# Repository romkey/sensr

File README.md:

# Sensr

Sensr is a group of hardware projects intended for environmental
sensing.

It currently consists of:
- base board - ESP32-S3 with accelerometer, I2S microphone header, display header, 2 Qwiic ports, particle counter connector
- air - SCD40 CO2 + BME680 temperature/humidity/pressure sensor
- air-stcc4 - new STCC4 CO2 sensor + SHT40 temperature/humidity sensor
- light - TSL25911 light
- light-ltr390uv - LTR390 UV sensor + TSL25911 light sensor

Sensr is an ESP32 S3-based microcontroller intended for environmental sensing, as well as separate sensor boards.

## I2C Addresses

0x29 TSL25911
0x74 AS7331
0x49 AS7341
0x53 LT-390 

0x76 BME680
0x62 SCD40
0x59 SGP40
0x5D SFA30
0x44 SHT3X-D

0x6A LSM6DS3TR-C 

Gas:
0x64
0x65
0x66
0x67
0x68
0x69
0x6B

# bodged I2S
SCK - CS - 10
SD - RESET - 9
WS - DC - 46
L/R - SDI (MOSI) - 16

## License

Hardware is shared under the [CERN-OHL-S-2.0](CERN_OHL_S_v2.txt) license.

Software is shared under the [MIT license](MIT-LICENSE.txt).

Documentation is shared under the [CC-BY-SA-4.0](CC-BY-SA-4.0.txt) - Attribution-ShareAlike license.

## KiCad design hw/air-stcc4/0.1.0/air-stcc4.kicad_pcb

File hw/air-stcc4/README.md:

# Sensr Air STCC4

This breakout board has Sensirion's new CO2 sensor, the STCC4, as well as an SHT40 temperature/humidity sensor. The board also has two STEMMAQT/Qwiic connectors and a five pin header with power, I2C and the STCC4's address select pin.

This is a 3.3V board and has no voltage regulator, so don't use it with 5V circuits!

It also has a power LED.

The STCC4 has a selectable I2C address depending on the state of the ADDR line.  The ADDR line has a weak pulldown resistor so that the STCC4's default I2C address is 0x64. If ADDR is high, the address will be 0x65.

The SHT40 is not directly accessible from the I2C bus. Instead it connects to a private second I2C bus with the STCC4. Its values may be read through the STCC4.

## 0.1.0 Hardware

## Firmware

Example program in CircuitPython:

```
import time
import board
import busio
from adafruit_stcc4 import STCC4

# Initialize I2C bus
i2c = busio.I2C(board.SCL, board.SDA)

# Initialize STCC4 sensor
sensor = STCC4(i2c)

print("STCC4 CO2 Sensor Test")
print("=" * 50)

# Print sensor information
print(f"Serial Number: {sensor.serial_number}")
print(f"Firmware Version: {sensor.firmware_version[0]}.{sensor.firmware_version[1]}")
print(f"SHT40 Available: {sensor.sht40_available}")
print()

# Read CO2, temperature, and humidity measurements
print("Environmental Measurements:")
print("-" * 30)

while True:
    co2 = sensor.co2
    print(f"Reading {i+1:2d}: CO2: {co2:6.1f} ppm")
        
    if sensor.sht40_available:
       temperature, humidity = sensor.measure_temperature_humidity()
       print(f"           Temp: {temperature:5.1f}°C, Humidity: {humidity:5.1f}%")
    else:
       print("           SHT40 not available - no temp/humidity data")
        
    print()
        
    time.sleep(2)  # Wait 2 seconds between readings

print("Test complete!")
```

## License

Hardware is shared under the [CERN-OHL-S-2.0](CERN_OHL_S_v2.txt) license.

Software is shared under the [MIT license](MIT-LICENSE.txt).

Documentation is shared under the [CC-BY-SA-4.0](CC-BY-SA-4.0.txt) - Attribution-ShareAlike license.

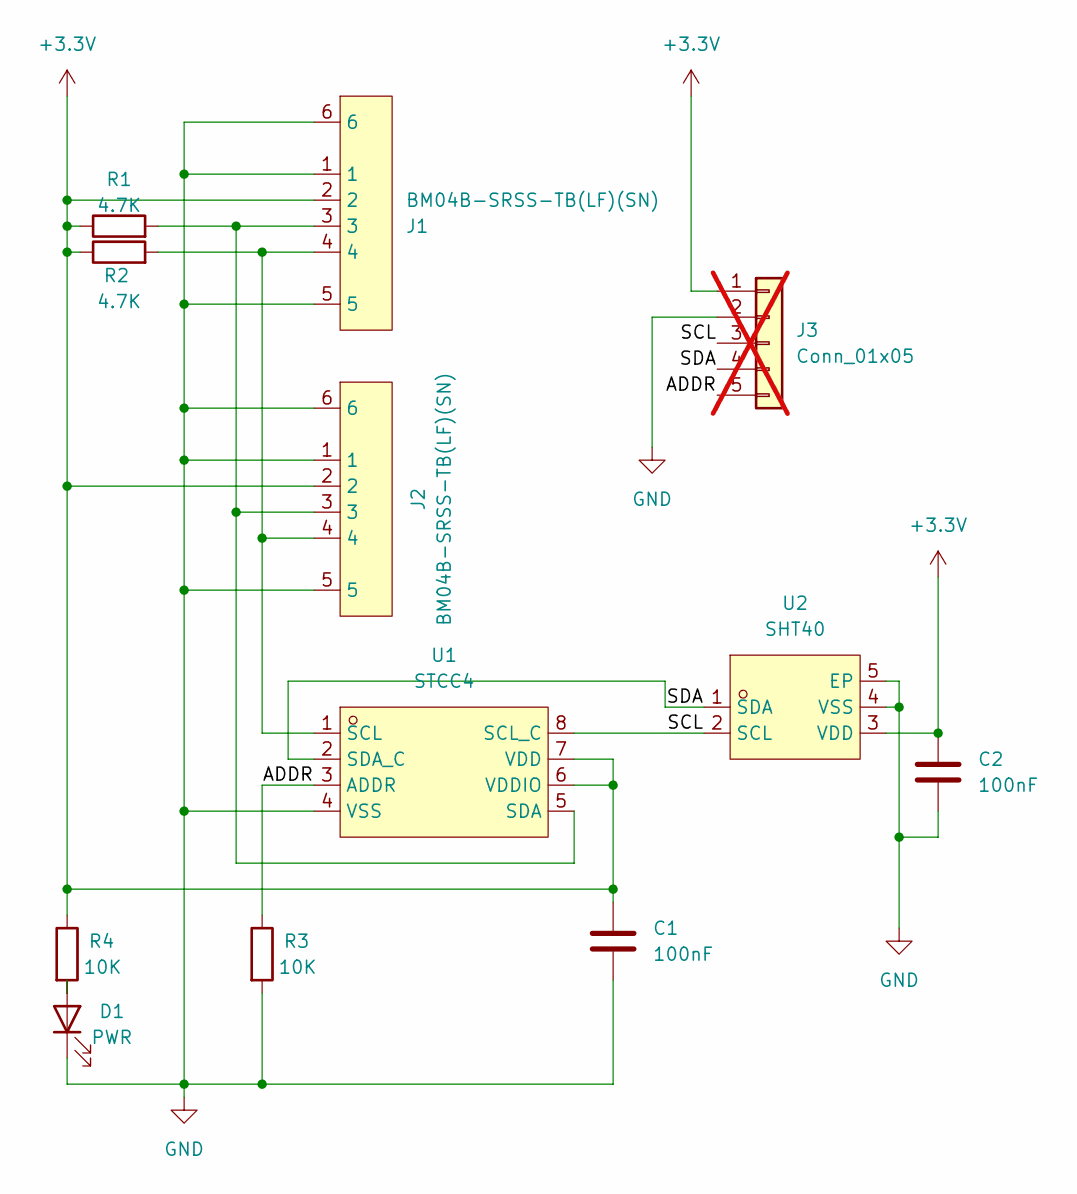
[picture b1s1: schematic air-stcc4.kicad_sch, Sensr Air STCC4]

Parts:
C1, C2: 100nF; C_0603_1608Metric_Pad1.08x0.95mm_HandSolder; MPN C14663
D1: PWR; LED_0201_0603Metric_Pad0.64x0.40mm_HandSolder; LCSC C2286
J1, J2: BM04B-SRSS-TB(LF)(SN); CONN-SMD_4P-P1.00_SM04B-SRSS-TB-LF-SN; LCSC Part C160404
J3: Conn_01x05; PinSocket_1x05_P2.54mm_Vertical; not fitted
R1, R2: 4.7K; R_0603_1608Metric_Pad0.98x0.95mm_HandSolder; MPN C23162
R3, R4: 10K; R_0603_1608Metric_Pad0.98x0.95mm_HandSolder; LCSC C25804
U1: STCC4; LAG-8_L4.0-W3.0-P1.15-TL; LCSC Part C49191471
U2: SHT40; DFN-4_L1.5-W1.5-P0.80-TL-EP; LCSC Part C7461861

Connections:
+3.3V: C1.1, C2.1, J1.2, J2.2, J3.1, R1.1, R2.1, R4.1, U1.6 (VDDIO), U1.7 (VDD), U2.3 (VDD)
/ADDR: J3.5, R3.1, U1.3 (ADDR)
/SCL: J3.3, U1.8 (SCL_C), U2.2 (SCL)
/SDA: J3.4, U1.2 (SDA_C), U2.1 (SDA)
GND: C1.2, C2.2, D1.1 (K), J1.1, J1.5, J1.6, J2.1, J2.5, J2.6, J3.2, R3.2, U1.4 (VSS), U2.4 (VSS), U2.5 (EP)
unnamed: D1.2 (A), R4.2
unnamed: J1.4, J2.4, R2.2, U1.1 (SCL)
unnamed: J1.3, J2.3, R1.2, U1.5 (SDA)

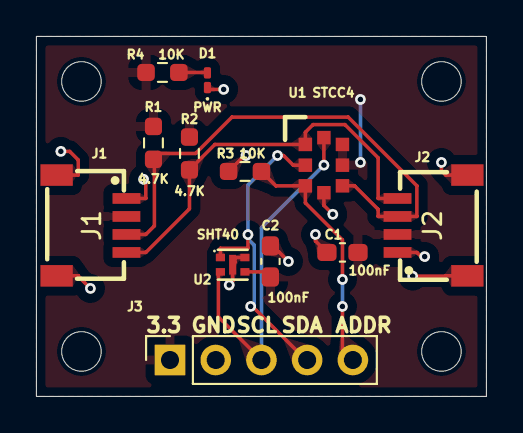
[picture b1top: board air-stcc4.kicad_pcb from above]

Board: 2 copper layers, 25.0 x 20.0 mm, 16 parts (0 on the bottom side), 8 nets.

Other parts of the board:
M1, M2, M3, M4: MountingHole_2.2mm_M2

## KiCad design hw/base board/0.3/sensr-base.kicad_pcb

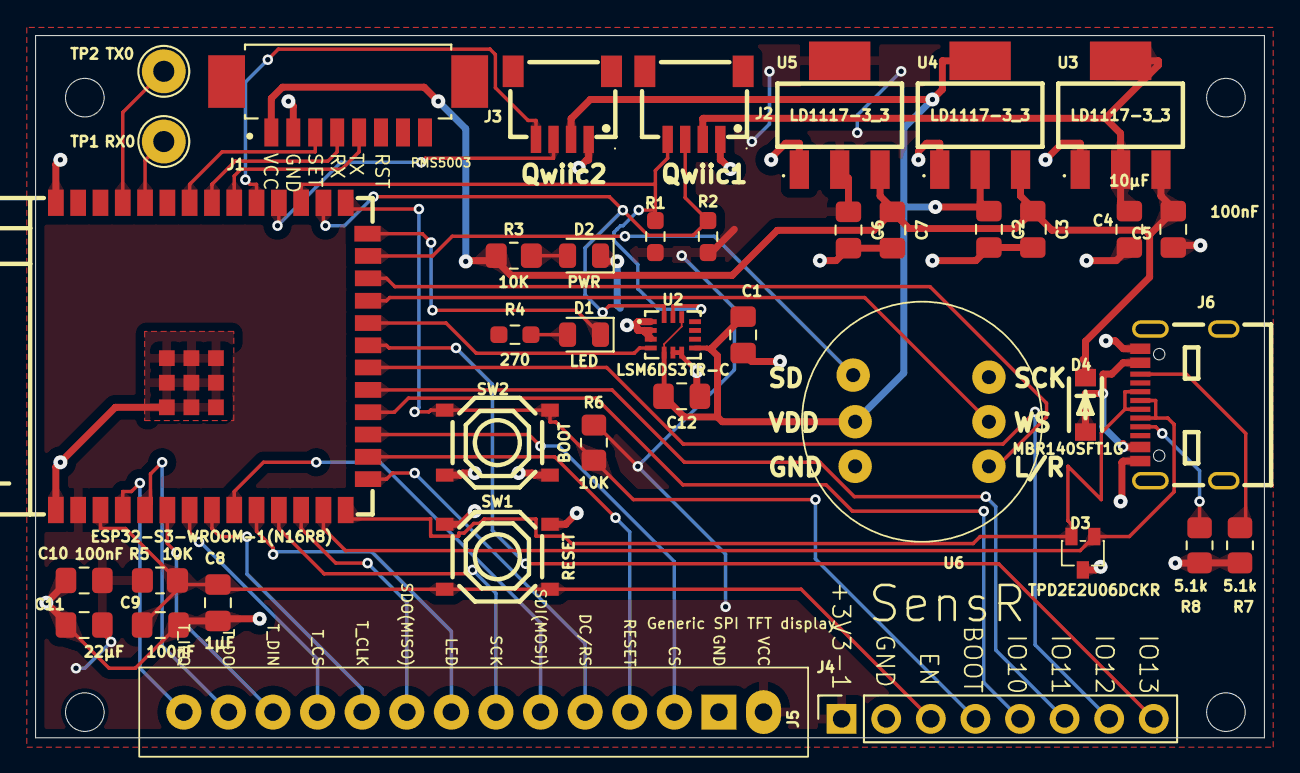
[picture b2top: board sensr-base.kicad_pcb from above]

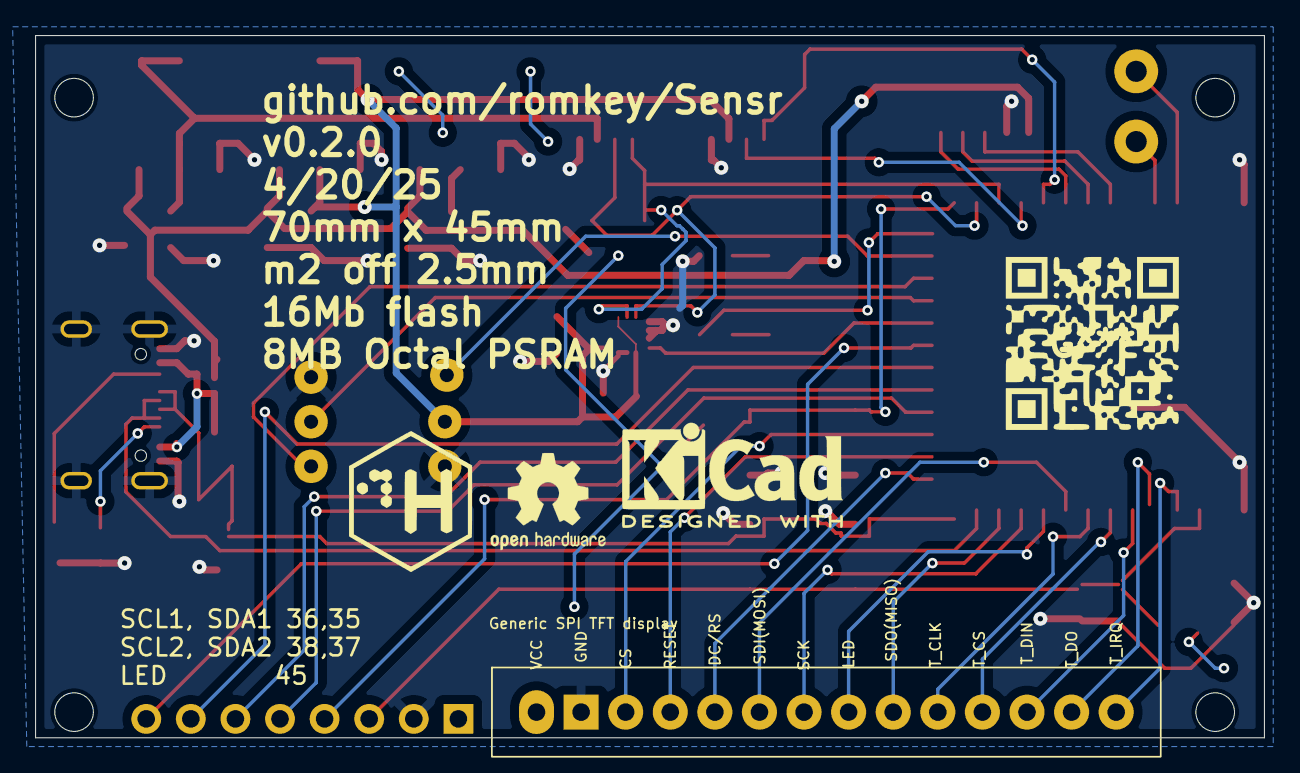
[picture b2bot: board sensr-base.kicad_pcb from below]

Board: 2 copper layers, 70.0 x 40.0 mm, 47 parts (3 on the bottom side), 44 nets.

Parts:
C1, C3, C5, C7, C9, C10, C12: 100nF; C_0805_2012Metric_Pad1.18x1.45mm_HandSolder
C2, C4, C6: 10µF; C_0805_2012Metric_Pad1.18x1.45mm_HandSolder
C8: 1µF; C_0805_2012Metric_Pad1.18x1.45mm_HandSolder
C11: 22µF; C_0805_2012Metric_Pad1.18x1.45mm_HandSolder
D1: LED; LED_0805_2012Metric
D2: PWR; LED_0805_2012Metric
D3: TPD2E2U06DCKR; SC-70-3_L2.0-W1.3-P0.65-LS2.1-BL
D4: MBR140SFT1G; SOD-123F_L2.8-W1.8-LS3.7-RD
J1: PMS5003 Connector
J2, J3: SM04B-SRSS-TB_(LF)(SN); CONN-SMD_4P-P1.00_SM04B-SRSS-TB-LF-SN
J4: SPI_TFT_TOUCH
J5: Conn_01x08_Pin; PinSocket_1x08_P2.54mm_Vertical
J6: TYPE-C-31-M-12; USB-C-SMD_MC-311D
M1, M2, M3, M4: MountingHole_2.2mm_M2_ISO7380
NOT2: CTRLH Logo
NOT3: KiCad-Logo2_5mm_SilkScreen
NOT4: OSHW-Logo2_7.3x6mm_SilkScreen
R1, R2: 4.7K; R_0603_1608Metric_Pad0.98x0.95mm_HandSolder
R3, R5, R6: 10K; R_0805_2012Metric_Pad1.20x1.40mm_HandSolder
R4: 270; R_0603_1608Metric_Pad0.98x0.95mm_HandSolder
R7, R8: 5.1k; R_0805_2012Metric_Pad1.20x1.40mm_HandSolder
SW1: RESET; SW-SMD_4P-L5.1-W5.1-P3.70-LS6.5-TL_H1.5
SW2: BOOT; SW-SMD_4P-L5.1-W5.1-P3.70-LS6.5-TL_H1.5
TP1: RX0; TestPoint_THTPad_D2.5mm_Drill1.2mm
TP2: TX0; TestPoint_THTPad_D2.5mm_Drill1.2mm
U1: ESP32-S3-WROOM-1(N16R8); WIRELM-SMD_ESP32-S3-WROOM-1
U2: LSM6DS3TR-C; LGA-14_L3.0-W2.5-P0.50-TL
U3, U4, U5: LD1117-3_3; SOT-223_L6.7-W3.5-P2.30-BR
U6: INMP4

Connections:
+3V3-1: C6.1, C10.1, C11.1, J4.1 (VCC), J5.1, R1.1, R2.1, R5.1, R6.1, U1.2 (3V3), U5.2 (VOUT(TAB)), U5.4 (TAB)
+3V3-2: C1.1, C2.1, C12.1, J3.2, U2.5 (VDDIO), U2.8 (VDD), U2.12 (CS), U4.2 (VOUT(TAB)), U4.4 (TAB), U6.2 (VDD)
+3V3-3: C4.1, J2.2, U3.2 (VOUT(TAB)), U3.4 (TAB)
+5V: C3.1, C5.1, C7.1, D4.1 (K), J1.1 (5V), R3.1, U3.3 (IN), U4.3 (IN), U5.3 (IN)
/ACC_INT: U1.22 (IO14), U2.4 (INT1)
/BCKLT: J4.8 (LED), U1.10 (IO17)
/BOOT: J5.4, R6.2, SW2.1 (A), SW2.2 (B), U1.27 (IO0)
/CS: J4.3 (CS), U1.17 (IO9)
/D+: D3.2 (IO2), J6.A6 (DP1), J6.B6 (DP2), U1.14 (IO20)
/D-: D3.1 (IO1), J6.A7 (DN1), J6.B7 (DN2), U1.13 (IO19)
/DCRS: J4.5 (DC/RS), U1.15 (IO3)
/DSP_RST: J4.4 (RESET), U1.16 (IO46)
/EN: C8.1, C9.1, J5.3, R5.2, SW1.1 (A), SW1.2 (B), U1.3 (EN)
/IO10: J5.5, U1.18 (IO10)
/IO11: J5.6, U1.19 (IO11)
/IO12: J5.7, U1.20 (IO12)
/IO13: J5.8, U1.21 (IO13)
/LED: D1.1 (K), U1.26 (IO45)
/MIC_CLK: U1.24 (IO47), U6.6 (CLK)
/MIC_DAT: U1.25 (IO48), U6.3 (SD)
/MIC_WS: U1.23 (IO21), U6.5 (WS)
/PM_RX: J1.4 (RX), U1.33 (IO40)
/PM_SET: J1.3 (SET), U1.34 (IO41)
/PM_TX: J1.5 (TX), U1.32 (IO39)
/RX0: TP1.1, U1.36 (RXD0)
/SCK: J4.7 (SCK), U1.11 (IO18)
/SCL1: J2.4, R1.2, U1.29 (IO36), U2.13 (SCL)
/SCL2: J3.4, U1.31 (IO38)
/SDA1: J2.3, R2.2, U1.28 (IO35), U2.14 (SDA)
/SDA2: J3.3, U1.30 (IO37)
/SDI: J4.9 (SDO_(MISO)), U1.12 (IO8)
/SDO: J4.6 (SDI_(MOSI)), U1.9 (IO16)
/TX0: TP2.1, U1.37 (TXD0)
/T_CLK: J4.10 (T_CLK), U1.8 (IO15)
/T_CS: J4.11 (T_CS), U1.7 (IO7)
/T_DIN: J4.12 (T_DIN), U1.6 (IO6)
/T_DO: J4.13 (T_DO), U1.5 (IO5)
/T_IRQ: J4.14 (T_IRQ), U1.4 (IO4)
GND: C1.2, C2.2, C3.2, C4.2, C5.2, C6.2, C7.2, C8.2, C9.2, C10.2, C11.2, C12.2, D2.1 (K), D3.3 (GND), J1.2 (GND), J2.1, J3.1, J4.2 (GND), J5.2, J6.1 (SHIELD), J6.2 (SHIELD), J6.3 (SHIELD), J6.4 (SHIELD), J6.A1-B12 (GND), J6.B1-A12 (GND), R7.2, R8.2, SW1.3 (C), SW1.4 (D), SW2.3 (C), SW2.4 (D), U1.1 (GND), U1.40 (GND), U1.41 (GND), U2.1 (SDO/SA0), U2.2 (SDx), U2.3 (SCx), U2.6 (GND), U2.7 (GND), U3.1 (ADJ(GND)), U4.1 (ADJ(GND)), U5.1 (ADJ(GND)), U6.1 (GND), U6.4 (L/R)
unnamed: D1.2 (A), R4.2
unnamed: D2.2 (A), R3.2
unnamed: J6.A5 (CC1), R8.1
unnamed: J6.B5 (CC2), R7.1
VBUS: D4.2 (A), J6.A4-B9 (VBUS), J6.B4-A9 (VBUS)

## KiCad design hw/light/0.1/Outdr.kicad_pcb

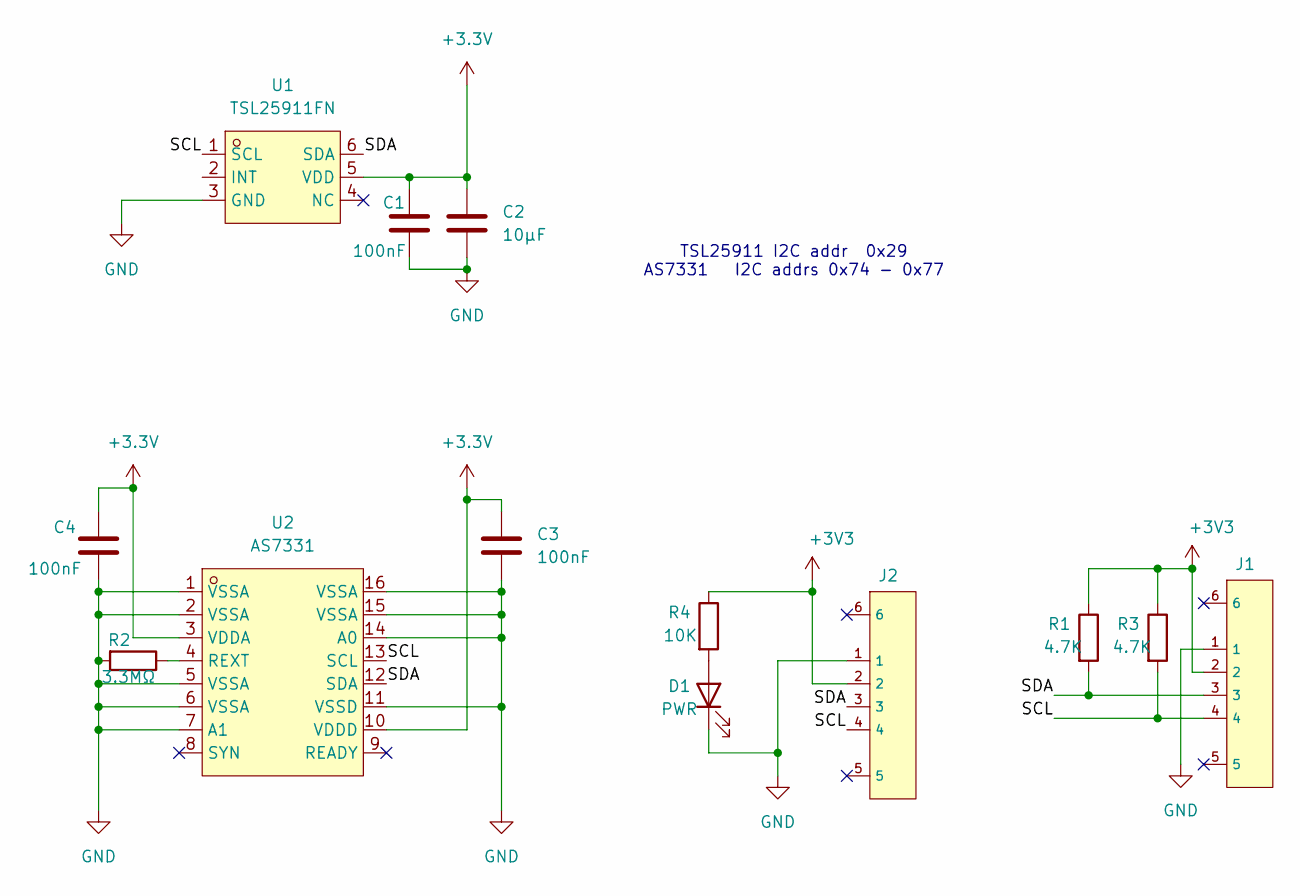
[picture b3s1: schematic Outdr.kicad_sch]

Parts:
C1, C3, C4: 100nF; C_0805_2012Metric_Pad1.18x1.45mm_HandSolder; MPN C1711
C2: 10µF; C_0805_2012Metric_Pad1.18x1.45mm_HandSolder; MPN C1713
D1: PWR; LED_0805_2012Metric; LCSC C84256
J1, J2: SM04B-SRSS-TB_(LF)(SN); CONN-SMD_4P-P1.00_SM04B-SRSS-TB-LF-SN; LCSC C160404
R1, R3: 4.7K; R_0805_2012Metric_Pad1.20x1.40mm_HandSolder; LCSC C17673
R2: 3.3MΩ; R_0805_2012Metric_Pad1.20x1.40mm_HandSolder; MPN C34154
R4: 10K; R_0805_2012Metric_Pad1.20x1.40mm_HandSolder; LCSC C17414
U1: TSL25911FN; DFN-6_L2.4-W2.0-P0.65-BL; LCSC Part C176812
U2: AS7331; OLGA-16_L3.7-W2.6-P0.50-TL_AS7331-AQFM; LCSC Part C7529330

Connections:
+3.3V: C1.1, C2.1, C3.1, C4.1, U1.5 (VDD), U2.3 (VDDA), U2.10 (VDDD)
+3V3: J1.2, J2.2, R1.1, R3.1, R4.1
/SCL: J1.4, J2.4, R3.2, U1.1 (SCL), U2.13 (SCL)
/SDA: J1.3, J2.3, R1.2, U1.6 (SDA), U2.12 (SDA)
GND: C1.2, C2.2, C3.2, C4.2, D1.1 (K), J1.1, J2.1, R2.2, U1.3 (GND), U2.1 (VSSA), U2.2 (VSSA), U2.5 (VSSA), U2.6 (VSSA), U2.7 (A1), U2.11 (VSSD), U2.14 (A0), U2.15 (VSSA), U2.16 (VSSA)
unnamed: D1.2 (A), R4.2
unnamed: R2.1, U2.4 (REXT)

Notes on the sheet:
TSL25911 I2C addr 0x29 AS7331 I2C addrs 0x74 - 0x77

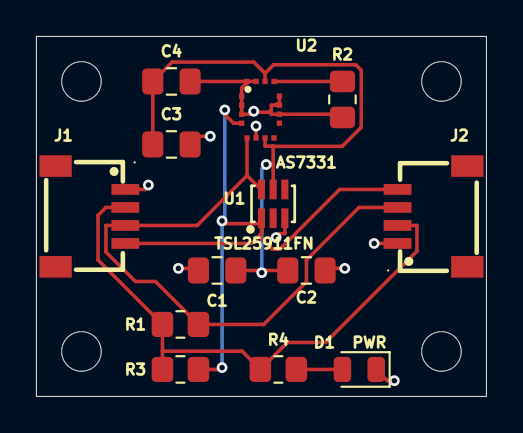
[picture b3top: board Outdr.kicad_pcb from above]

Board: 2 copper layers, 25.0 x 20.0 mm, 17 parts (0 on the bottom side), 7 nets.

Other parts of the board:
M1, M2, M3, M4: MountingHole_2.2mm_M2

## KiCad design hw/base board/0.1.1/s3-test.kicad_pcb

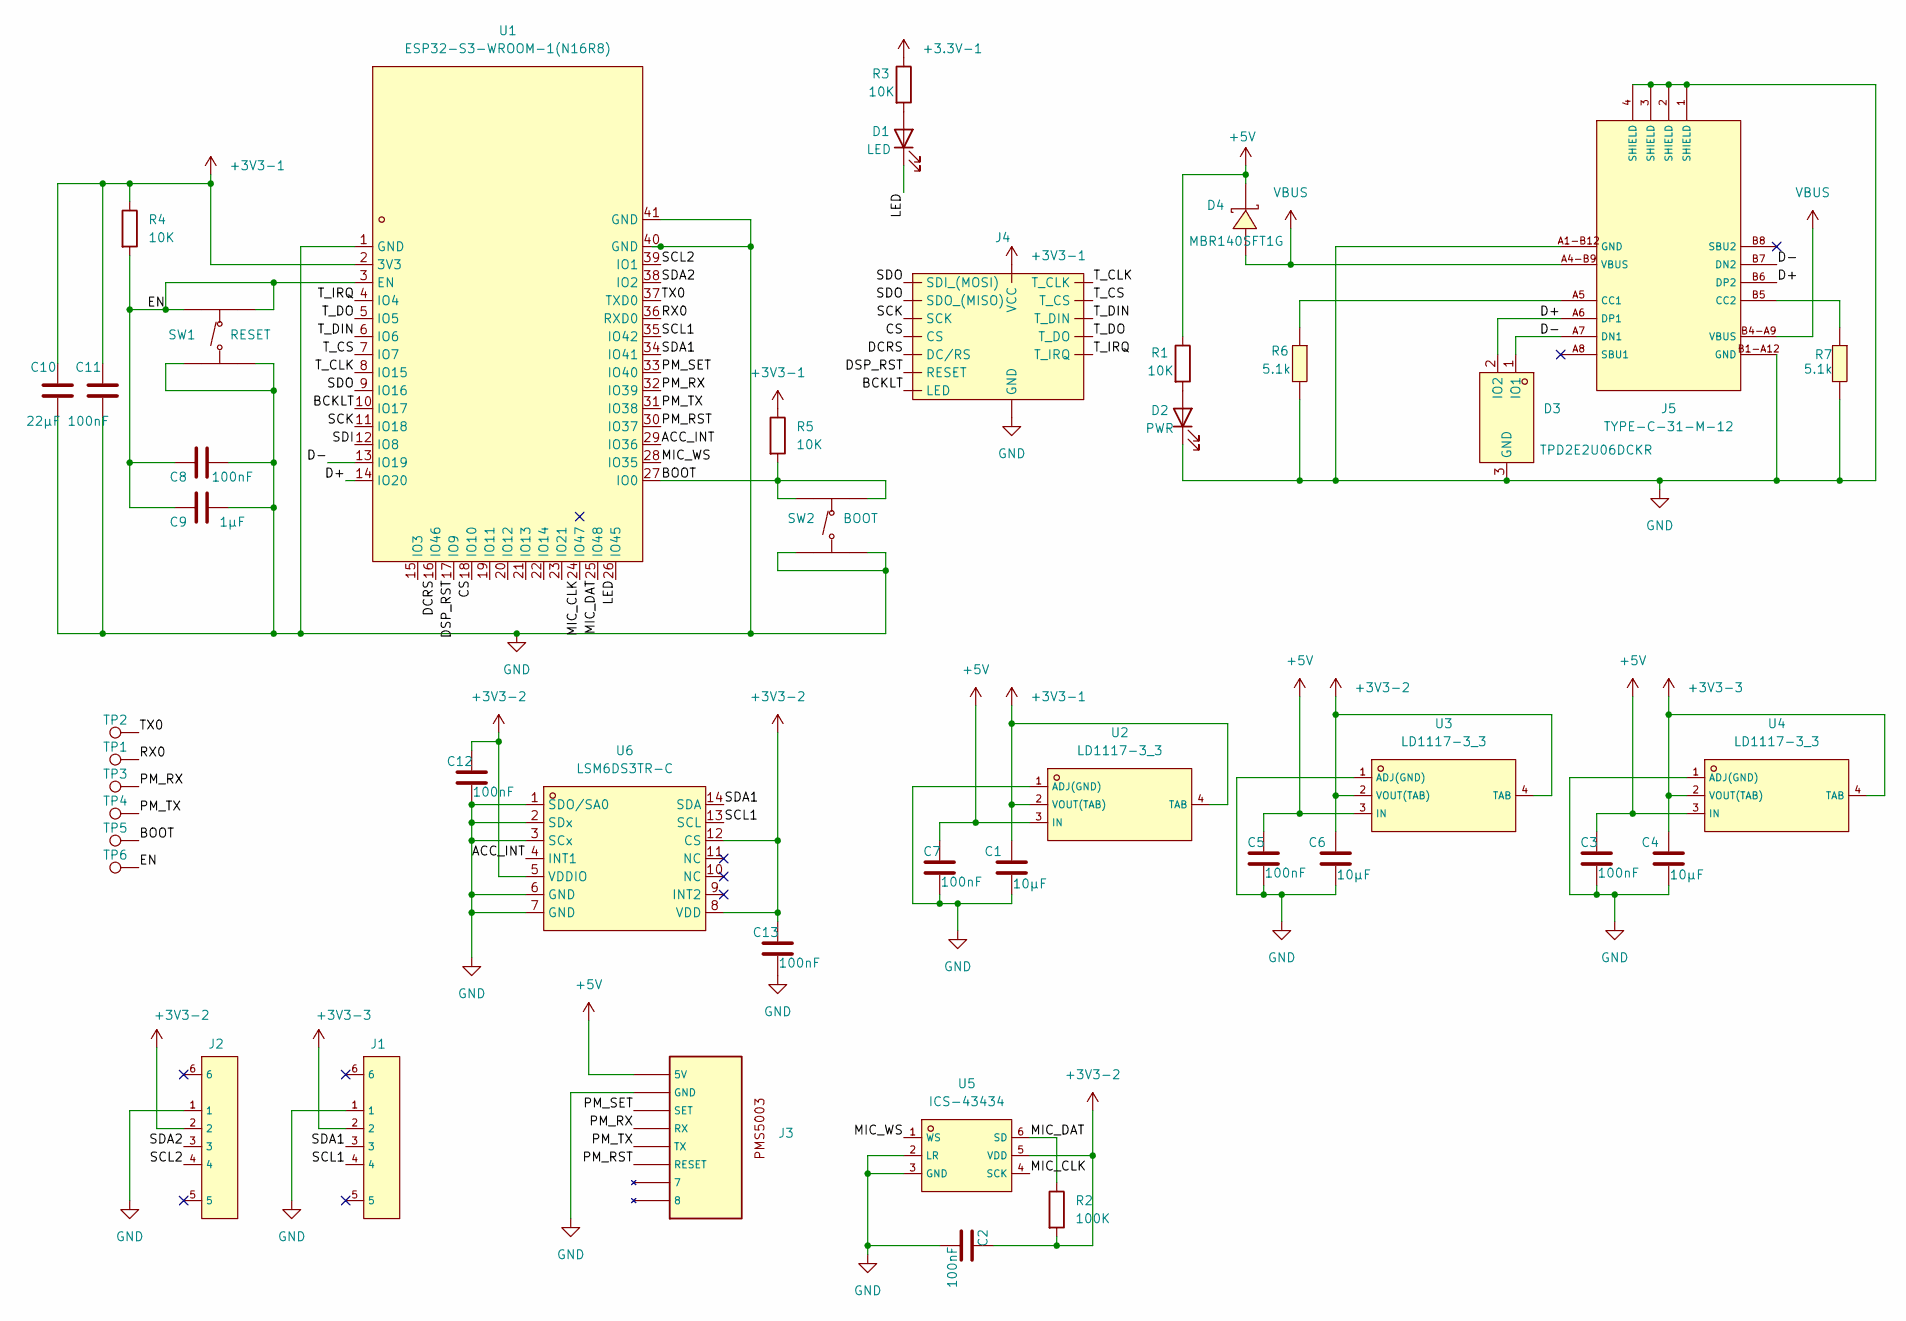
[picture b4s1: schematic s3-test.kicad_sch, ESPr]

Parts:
C1, C4, C6: 10µF; C_0805_2012Metric_Pad1.18x1.45mm_HandSolder; LCSC C1713
C2, C3, C5, C7, C8, C11, C12, C13: 100nF; C_0805_2012Metric_Pad1.18x1.45mm_HandSolder; LCSC C1711
C9: 1µF; C_0805_2012Metric_Pad1.18x1.45mm_HandSolder; LCSC C1712
C10: 22µF; C_0805_2012Metric_Pad1.18x1.45mm_HandSolder; LCSC C45783
D1: LED; LED_0805_2012Metric; LCSC C2297
D2: PWR; LED_0805_2012Metric; LCSC C84256
D3: TPD2E2U06DCKR; SC-70-3_L2.0-W1.3-P0.65-LS2.1-BL; LCSC Part C1855726
D4: MBR140SFT1G; SOD-123F_L2.8-W1.8-LS3.7-RD; LCSC C43381
J1, J2: SM04B-SRSS-TB_(LF)(SN); CONN-SMD_4P-P1.00_SM04B-SRSS-TB-LF-SN; LCSC C160404
J3: PMS5003 Connector; LCSC C293349
J4: SPI_TFT_TOUCH
J5: TYPE-C-31-M-12; USB-C-SMD_MC-311D; LCSC C136423
R1, R3, R4, R5: 10K; R_0805_2012Metric_Pad1.20x1.40mm_HandSolder; LCSC C17414
R2: 100K; R_0805_2012Metric_Pad1.20x1.40mm_HandSolder; LCSC C17414
R6, R7: 5.1k; R_0805_2012Metric_Pad1.20x1.40mm_HandSolder; LCSC C27834
SW1: RESET; SW-SMD_4P-L5.1-W5.1-P3.70-LS6.5-TL_H1.5; LCSC C318884
SW2: BOOT; SW-SMD_4P-L5.1-W5.1-P3.70-LS6.5-TL_H1.5; LCSC C318884
TP1: RX0; TestPoint_THTPad_D2.5mm_Drill1.2mm
TP2: TX0; TestPoint_THTPad_D2.5mm_Drill1.2mm
TP3: PM_RX; TestPoint_THTPad_D2.5mm_Drill1.2mm
TP4: PM_TX; TestPoint_THTPad_D2.5mm_Drill1.2mm
TP5: BOOT; TestPoint_THTPad_D2.5mm_Drill1.2mm
TP6: EN; TestPoint_THTPad_D2.5mm_Drill1.2mm
U1: ESP32-S3-WROOM-1(N16R8); WIRELM-SMD_ESP32-S3-WROOM-1; LCSC Part C2913202
U2, U3, U4: LD1117-3_3; SOT-223_L6.7-W3.5-P2.30-BR; LCSC C347229
U5: ICS-43434; MIC-SMD_6P-L3.5-W2.7-P0.90-BL; LCSC C5656610
U6: LSM6DS3TR-C; LGA-14_L3.0-W2.5-P0.50-TL; LCSC Part C967633

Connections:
+3.3V-1: R3.1
+3V3-1: C1.1, C10.1, C11.1, J4.1 (VCC), R4.1, R5.1, U1.2 (3V3), U2.2 (VOUT(TAB)), U2.4 (TAB)
+3V3-2: C2.1, C6.1, C12.1, C13.1, J2.2, R2.2, U3.2 (VOUT(TAB)), U3.4 (TAB), U5.5 (VDD), U6.5 (VDDIO), U6.8 (VDD), U6.12 (CS)
+3V3-3: C4.1, J1.2, U4.2 (VOUT(TAB)), U4.4 (TAB)
+5V: C3.1, C5.1, C7.1, D4.1 (K), J3.1 (5V), R1.1, U2.3 (IN), U3.3 (IN), U4.3 (IN)
/ACC_INT: U1.29 (IO36), U6.4 (INT1)
/BCKLT: J4.8 (LED), U1.10 (IO17)
/BOOT: R5.2, SW2.1 (A), SW2.2 (B), TP5.1, U1.27 (IO0)
/CS: J4.3 (CS), U1.18 (IO10)
/D+: D3.2 (IO2), J5.A6 (DP1), J5.B6 (DP2), U1.14 (IO20); also elsewhere on the board
/D-: D3.1 (IO1), J5.A7 (DN1), J5.B7 (DN2), U1.13 (IO19); also elsewhere on the board
/DCRS: J4.5 (DC/RS), U1.16 (IO46)
/DSP_RST: J4.4 (RESET), U1.17 (IO9)
/EN: C8.1, C9.1, R4.2, SW1.1 (A), SW1.2 (B), TP6.1, U1.3 (EN)
/LED: D1.1 (K), U1.26 (IO45)
/MIC_CLK: U1.24 (IO47), U5.4 (SCK)
/MIC_DAT: R2.1, U1.25 (IO48), U5.6 (SD)
/MIC_WS: U1.28 (IO35), U5.1 (WS)
/PM_RST: J3.6 (RESET), U1.30 (IO37)
/PM_RX: J3.4 (RX), TP3.1, U1.32 (IO39)
/PM_SET: J3.3 (SET), U1.33 (IO40)
/PM_TX: J3.5 (TX), TP4.1, U1.31 (IO38)
/RX0: TP1.1, U1.36 (RXD0)
/SCK: J4.7 (SCK), U1.11 (IO18)
/SCL1: J1.4, U1.35 (IO42), U6.13 (SCL)
/SCL2: J2.4, U1.39 (IO1)
/SDA1: J1.3, U1.34 (IO41), U6.14 (SDA)
/SDA2: J2.3, U1.38 (IO2)
/SDI: U1.12 (IO8)
/SDO: J4.6 (SDI_(MOSI)), J4.9 (SDO_(MISO)), U1.9 (IO16)
/TX0: TP2.1, U1.37 (TXD0)
/T_CLK: J4.10 (T_CLK), U1.8 (IO15)
/T_CS: J4.11 (T_CS), U1.7 (IO7)
/T_DIN: J4.12 (T_DIN), U1.6 (IO6)
/T_DO: J4.13 (T_DO), U1.5 (IO5)
/T_IRQ: J4.14 (T_IRQ), U1.4 (IO4)
GND: C1.2, C2.2, C3.2, C4.2, C5.2, C6.2, C7.2, C8.2, C9.2, C10.2, C11.2, C12.2, C13.2, D2.1 (K), D3.3 (GND), J1.1, J2.1, J3.2 (GND), J4.2 (GND), J5.1 (SHIELD), J5.2 (SHIELD), J5.3 (SHIELD), J5.4 (SHIELD), J5.A1-B12 (GND), J5.B1-A12 (GND), R6.2, R7.2, SW1.3 (C), SW1.4 (D), SW2.3 (C), SW2.4 (D), U1.1 (GND), U1.40 (GND), U1.41 (GND), U2.1 (ADJ(GND)), U3.1 (ADJ(GND)), U4.1 (ADJ(GND)), U5.2 (LR), U5.3 (GND), U6.1 (SDO/SA0), U6.2 (SDx), U6.3 (SCx), U6.6 (GND), U6.7 (GND); also elsewhere on the board
unnamed: D2.2 (A), R1.2
unnamed: D1.2 (A), R3.2
unnamed: J5.A5 (CC1), R6.1
unnamed: J5.B5 (CC2), R7.1
VBUS: D4.2 (A), J5.A4-B9 (VBUS), J5.B4-A9 (VBUS)

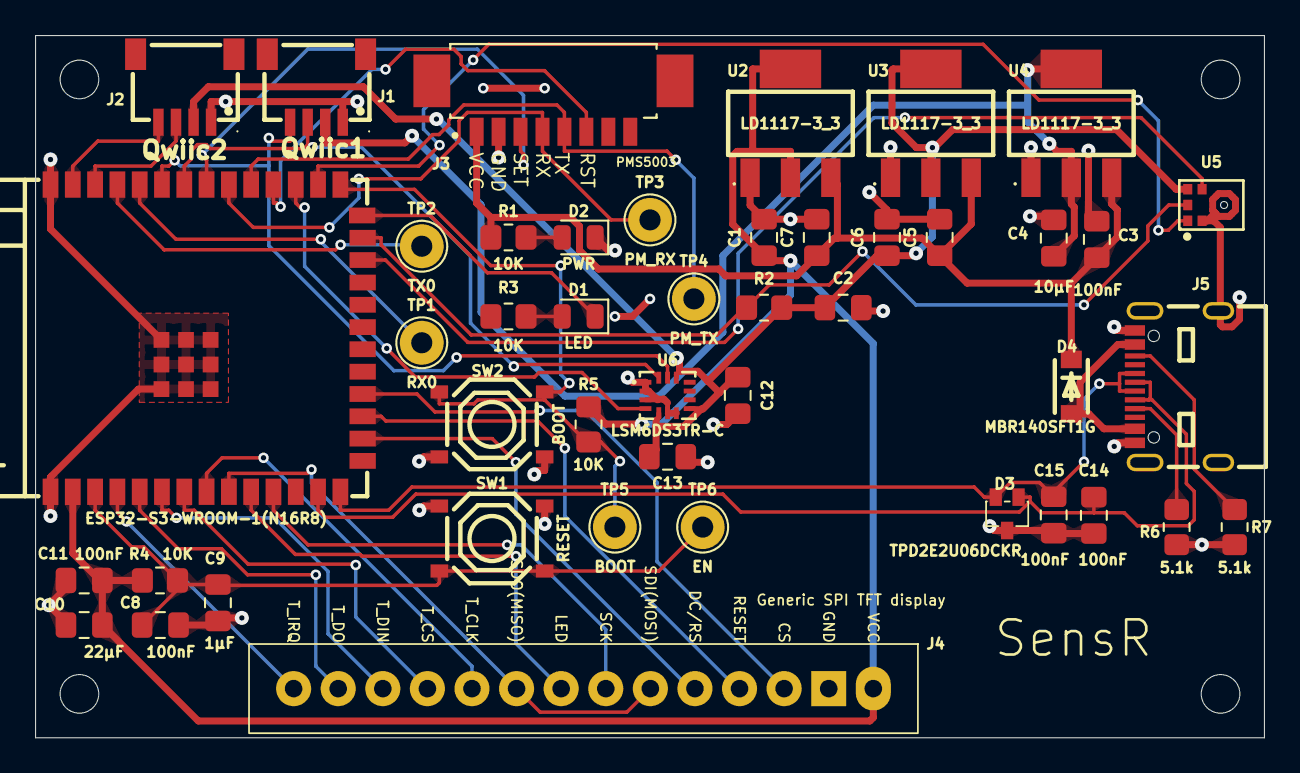
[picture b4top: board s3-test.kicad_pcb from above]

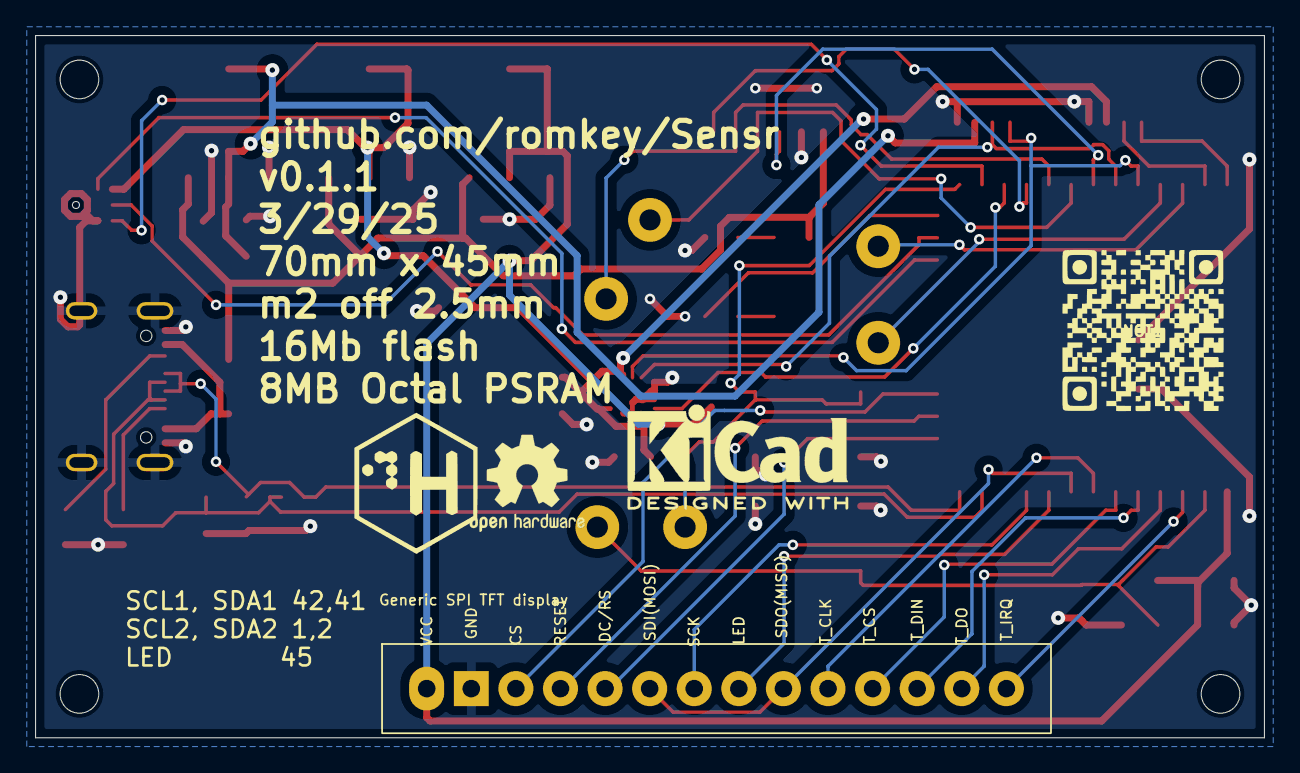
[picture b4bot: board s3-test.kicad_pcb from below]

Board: 2 copper layers, 70.0 x 40.0 mm, 53 parts (4 on the bottom side), 40 nets.

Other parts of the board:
C14, C15: 100nF; C_0805_2012Metric_Pad1.18x1.45mm_HandSolder
M1, M2, M3, M4: MountingHole_2.2mm_M2_ISO7380
NOT1: LOGO
NOT2: CTRLH Logo
NOT3: KiCad-Logo2_5mm_SilkScreen
NOT4: OSHW-Logo2_7.3x6mm_SilkScreen

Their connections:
/D+: C15.1; also elsewhere on the board
/D-: C14.1; also elsewhere on the board
GND: C14.2, C15.2; also elsewhere on the board

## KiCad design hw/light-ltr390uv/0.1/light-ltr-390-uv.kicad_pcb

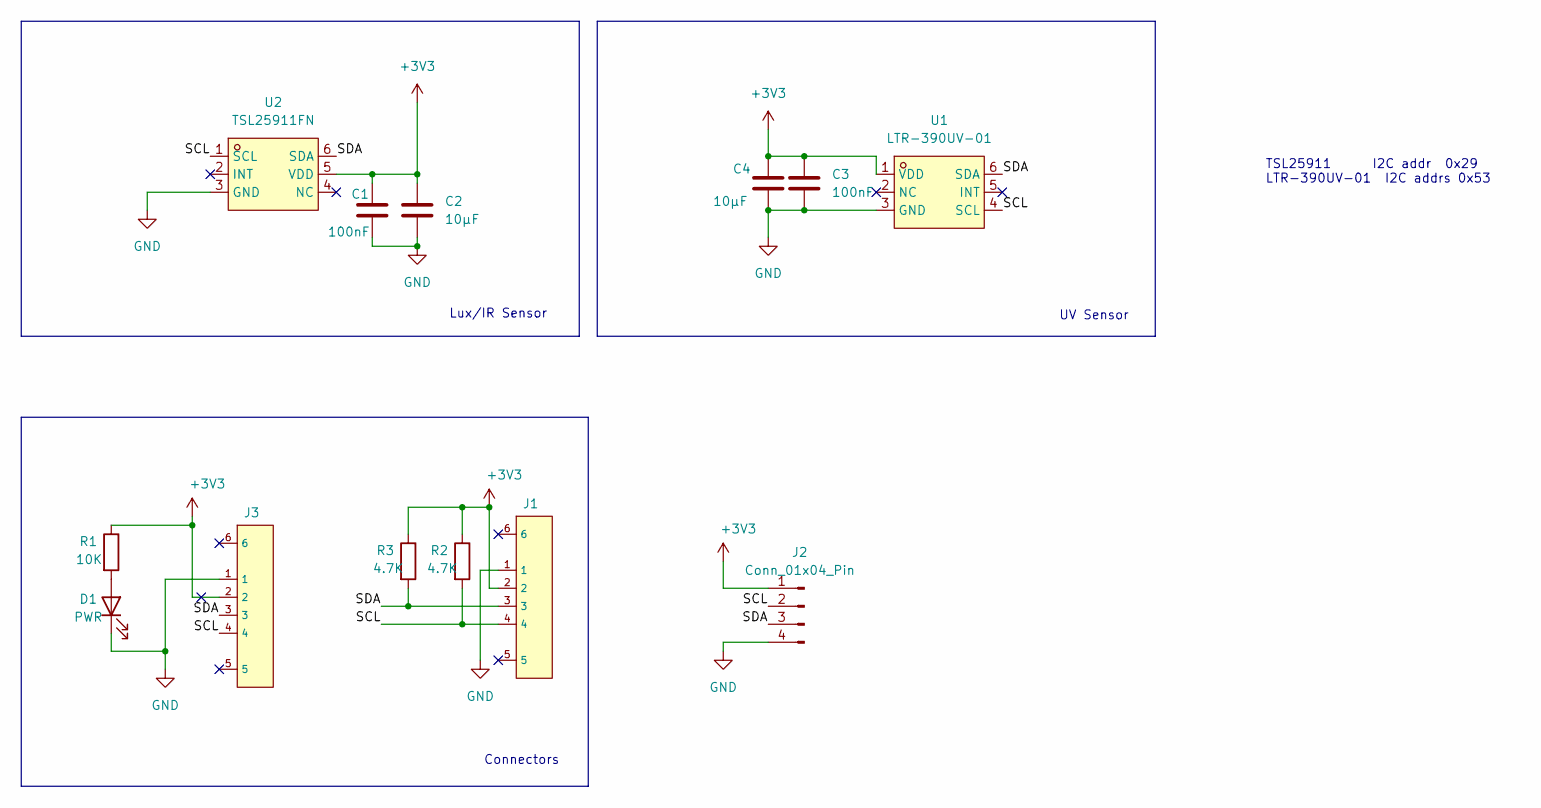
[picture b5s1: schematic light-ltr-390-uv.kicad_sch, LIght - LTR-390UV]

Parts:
C1, C3: 100nF; C_0805_2012Metric_Pad1.18x1.45mm_HandSolder; MPN C1711
C2, C4: 10µF; C_0805_2012Metric_Pad1.18x1.45mm_HandSolder; MPN C1713
D1: PWR; LED_0805_2012Metric; LCSC C84256
J1, J3: SM04B-SRSS-TB_(LF)(SN); CONN-SMD_4P-P1.00_SM04B-SRSS-TB-LF-SN; LCSC C160404
J2: Conn_01x04_Pin; PinHeader_1x04_P2.54mm_Vertical
R1: 10K; R_0805_2012Metric_Pad1.20x1.40mm_HandSolder; LCSC C17414
R2, R3: 4.7K; R_0805_2012Metric_Pad1.20x1.40mm_HandSolder; LCSC C17673
U1: LTR-390UV-01; SENSOR-SMD_LTR-390UV-01; LCSC Part C492374
U2: TSL25911FN; DFN-6_L2.4-W2.0-P0.65-BL; LCSC Part C176812

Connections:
+3V3: C1.1, C2.1, C3.1, C4.1, J1.2, J2.1, J3.2, R1.1, R2.1, R3.1, U1.1 (VDD), U2.5 (VDD)
/SCL: J1.4, J2.2, J3.4, R2.2, U1.4 (SCL), U2.1 (SCL)
/SDA: J1.3, J2.3, J3.3, R3.2, U1.6 (SDA), U2.6 (SDA)
GND: C1.2, C2.2, C3.2, C4.2, D1.1 (K), J1.1, J2.4, J3.1, U1.3 (GND), U2.3 (GND)
unnamed: D1.2 (A), R1.2

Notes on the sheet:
TSL25911 I2C addr 0x29 LTR-390UV-01 I2C addrs 0x53
Connectors
UV Sensor
Lux/IR Sensor

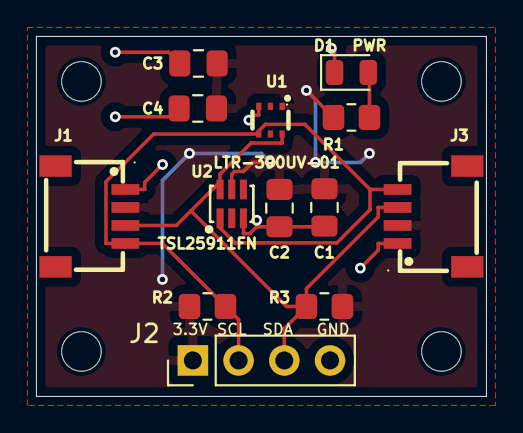
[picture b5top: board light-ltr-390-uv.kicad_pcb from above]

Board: 2 copper layers, 25.0 x 20.0 mm, 17 parts (0 on the bottom side), 5 nets.

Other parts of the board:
M1, M2, M3, M4: MountingHole_2.2mm_M2

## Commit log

2025-08-14 license, code of conduct
2025-09-17 updated docs, added detailed pinout for 0.2.0
2025-09-23 initial commit for air-stcc4
2025-09-24 added CTRLH logo ; fixed MPN for 10K resistors
2025-09-28 doc improvements
    fixed LED footprint on air-stcc4/0.1.0 (changed to 0603)
